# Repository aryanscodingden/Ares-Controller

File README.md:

## Ares - A game controller
A custom game controller built using a ESP32. 

This project was built because I always wanted to own a controller & decided to build one instead. 
It was indeed a very intersting journey to build one of my own, started to appricate the small QOL of other products.
<br>
(P.S. This is my first ever hardware project)

# Schematic

This schematic was made in KiCAD. It's a very simple controller.
<br>
It features a ESP32-NodeMCU for the main controller board & a TP4056 Module to charge the entire controller.

# PCB

# Case
This case was designed in Fusion 360. 

# Firmware

The firmware is written in C++ and will be edited/deployed from Arduino IDE.

# BOM
| SR NO | Item | Unit Price | URL |
|------:|------|-----------:|-----|
| 1 | ESP 32 NODE-MCU | ₹383 ($4.06) | https://robocraze.com/products/nodemcu-32-wifi-bluetooth-esp32-development-board30-pin |
| 2 | Joysticks | ₹269 ($2.85) | https://www.amazon.in/Robocraze-Joystick-Module-PS2-Set/dp/B086VZH739 |
| 3 | TP4056 | ₹14 ($0.15) | https://robocraze.com/products/tp4056-battery-charger-c-type-module-with-protection-1 |
| 4 | Tactile Push Button Switch Assorted Kit | ₹156 ($1.65) | https://robocraze.com/products/tactile-push-button-switch-assorted-kit-25-pieces-pack |
| 5 | Right Angle Tactile Triggers | ₹383 ($4.06) | https://www.amazon.in/Push-Button-Tactile-Switch-Height/dp/B08P5BN7JM |
| 6 | SPST Switches | ₹74 ($0.78) | https://www.amazon.in/Panel-Mount-Momentary-Button-Switch/dp/B0B54XV8D2 |
| 7 | 18650 Battery | ₹217 ($2.30) | https://robu.in/product/bak-nmc-18650-2600mah-3c-lithium-ion-3-6v-battery/ |
| 8 | 18650 Battery Holder | ₹16 ($0.17) | https://robocraze.com/products/18650-1-cell-holder |
| 9 | PCB | ₹2,138 ($22.61) | robu.in |
| 10 | 3D Print | ₹699 ($7.08) | https://www.amazon.in/PLA-3D-Flexibility-Eco-Friendly-Compatible/dp/B071D82LDV |
| **Total** |  | **₹4,349 ($45)** | |

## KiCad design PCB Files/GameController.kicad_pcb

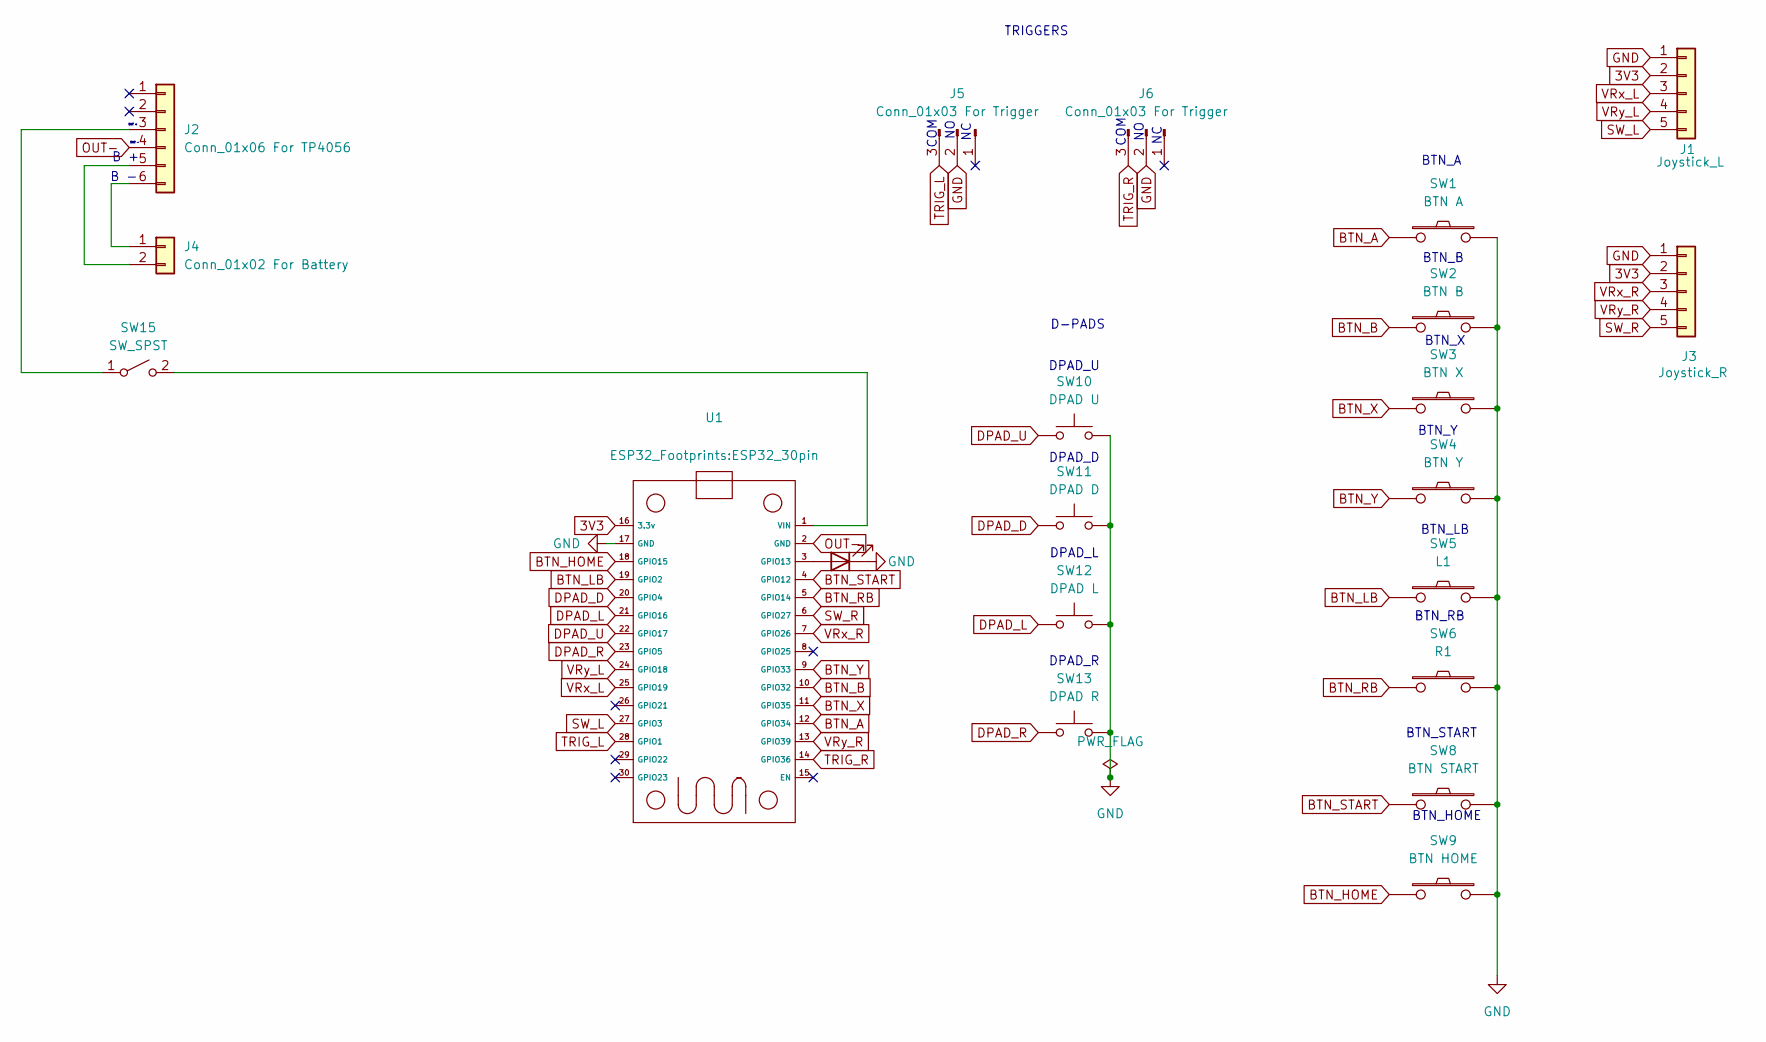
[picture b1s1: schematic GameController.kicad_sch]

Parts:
D1: LED; LED_D5.0mm_Horizontal_O6.35mm_Z3.0mm
J1: Joystick_L; PinHeader_1x05_P2.54mm_Horizontal
J2: Conn_01x06 For TP4056; TP4056-Module
J3: Joystick_R; PinHeader_1x05_P2.54mm_Horizontal
J4: Conn_01x02 For Battery; PinHeader_1x02_P2.54mm_Vertical
J5, J6: Conn_01x03 For Trigger
SW1: BTN A; SW_VS-1213-67-160GF
SW2: BTN B; SW_VS-1213-67-160GF
SW3: BTN X; SW_VS-1213-67-160GF
SW4: BTN Y; SW_VS-1213-67-160GF
SW5: L1; SW_Tactile_SKHH_Angled
SW6: R1; SW_Tactile_SKHH_Angled
SW8: BTN START; SW_VS-1213-67-160GF
SW9: BTN HOME; SW_VS-1213-67-160GF
SW10: DPAD U; SW_VS-1213-67-160GF
SW11: DPAD D; SW_VS-1213-67-160GF
SW12: DPAD L; SW_VS-1213-67-160GF
SW13: DPAD R; SW_VS-1213-67-160GF
SW15: SW_SPST; PinHeader_1x02_P2.54mm_Vertical
U1: ESP32_30pin

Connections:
3V3: J1.2, J3.2, U1.16 (3.3v)
BTN_A: SW1.1, U1.12 (GPIO34)
BTN_B: SW2.1, U1.10 (GPIO32)
BTN_HOME: SW9.1, U1.18 (GPIO15)
BTN_LB: SW5.1, U1.19 (GPIO2)
BTN_RB: SW6.1, U1.5 (GPIO14)
BTN_START: SW8.1, U1.4 (GPIO12)
BTN_X: SW3.1, U1.11 (GPIO35)
BTN_Y: SW4.1, U1.9 (GPIO33)
DPAD_D: SW11.1, U1.20 (GPIO4)
DPAD_L: SW12.1, U1.21 (GPIO16)
DPAD_R: SW13.1, U1.23 (GPIO5)
DPAD_U: SW10.1, U1.22 (GPIO17)
GND: D1.1 (K), J1.1, J3.1, J5.2, J6.2, SW1.2, SW2.2, SW3.2, SW4.2, SW5.2, SW6.2, SW8.2, SW9.2, SW10.2, SW11.2, SW12.2, SW13.2, U1.17 (GND)
unnamed: D1.2 (A), U1.3 (GPIO13)
unnamed: J2.3, SW15.1 (A)
unnamed: J2.5, J4.2
unnamed: J2.6, J4.1
unnamed: SW15.2 (B), U1.1 (VIN)
OUT-: J2.4, U1.2 (GND)
SW_L: J1.5, U1.27 (GPIO3)
SW_R: J3.5, U1.6 (GPIO27)
TRIG_L: J5.3, U1.28 (GPIO1)
TRIG_R: J6.3, U1.14 (GPIO36)
VRx_L: J1.3, U1.25 (GPIO19)
VRx_R: J3.3, U1.7 (GPIO26)
VRy_L: J1.4, U1.24 (GPIO18)
VRy_R: J3.4, U1.13 (GPIO39)

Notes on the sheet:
DPAD_L
DPAD_D
BTN_LB
BTN_A
B -
DPAD_R
BTN_Y
B +
BTN_START
DPAD_U
BTN_RB
COM
D-PADS
OUT +
OUT -
TRIGGERS
BTN_B
BTN_HOME
BTN_X

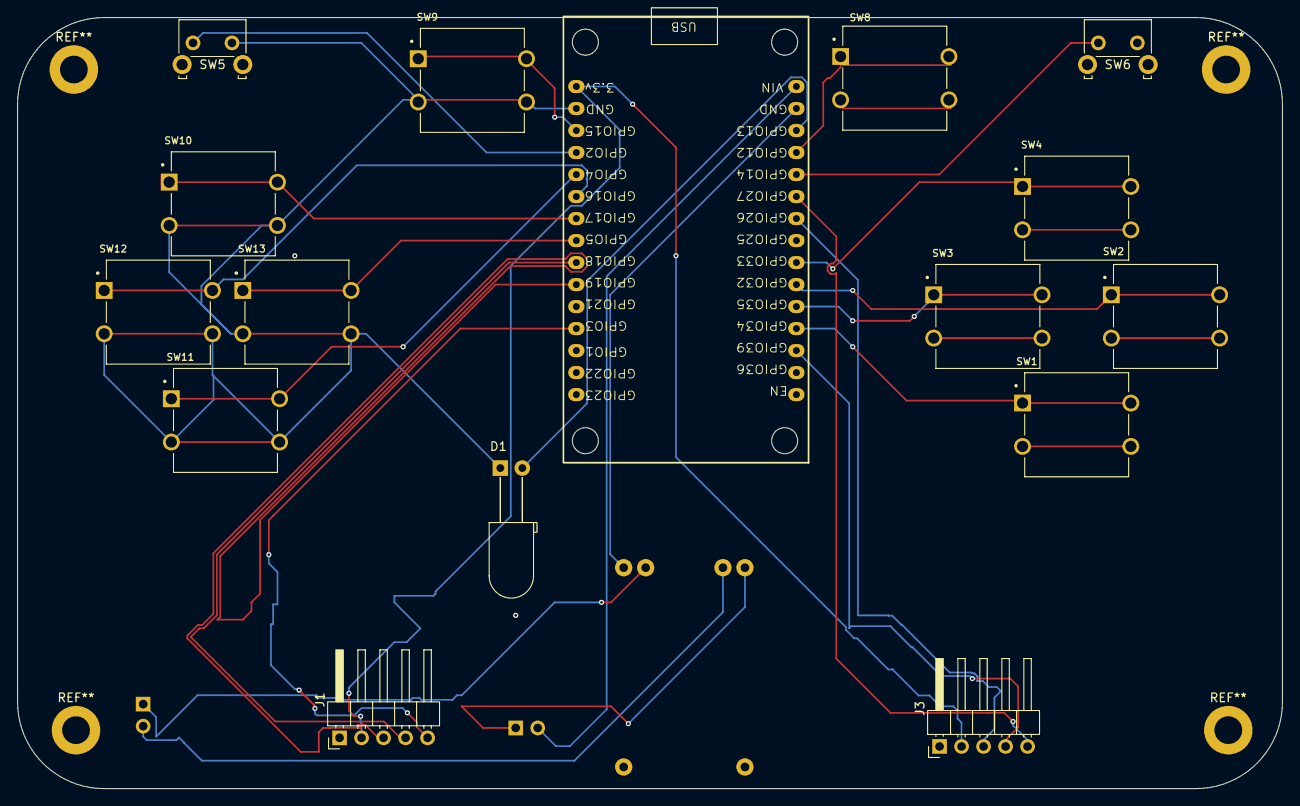
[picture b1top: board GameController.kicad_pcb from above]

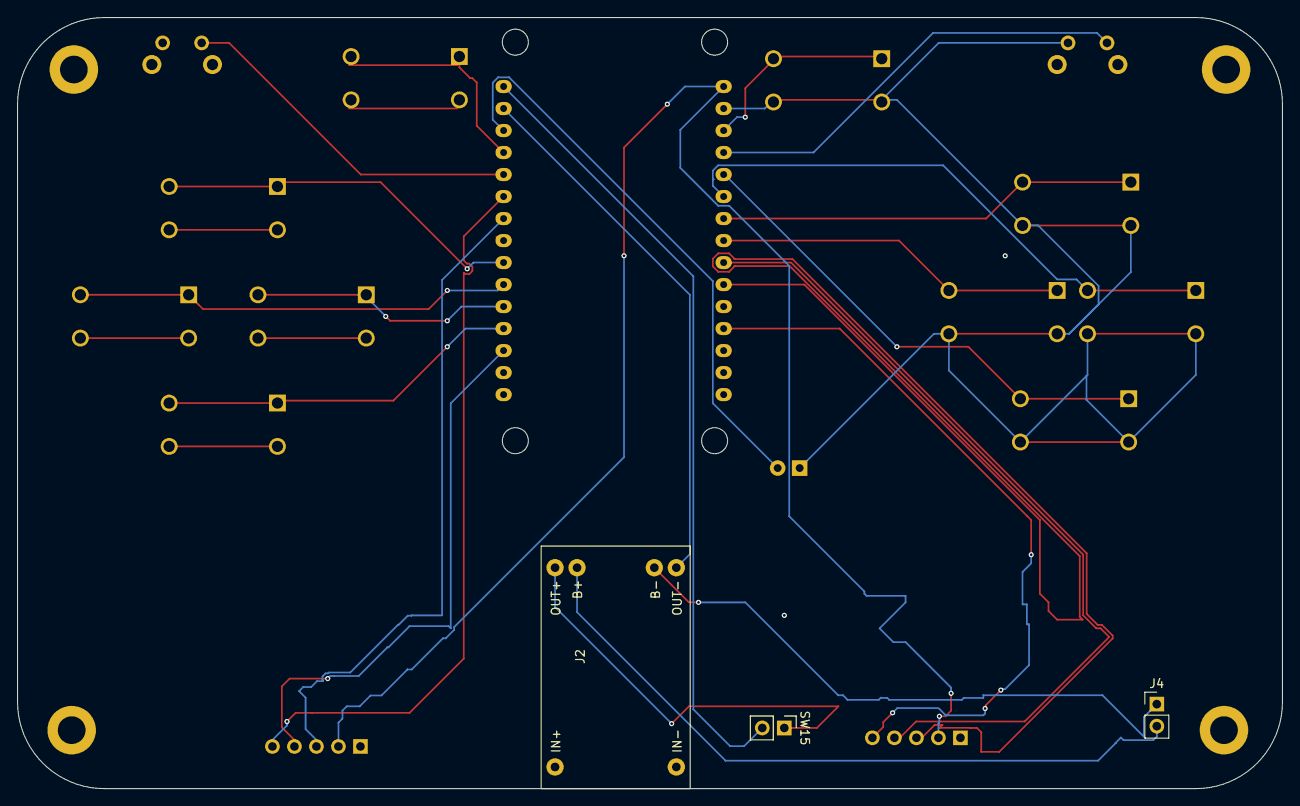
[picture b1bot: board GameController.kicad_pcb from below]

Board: 2 copper layers, 146.0 x 89.0 mm, 19 parts (3 on the bottom side), 26 nets.

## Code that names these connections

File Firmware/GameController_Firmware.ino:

#include <BleGamepad.h>
// Initialize BLE Gamepad as Xbox Controller
BleGamepad bleGamepad("Xbox Wireless Controller", "Microsoft", 100);
// ESP32-C6 Analog Pin Mapping (Joysticks Only)
#define LEFT_STICK_X 39
#define LEFT_STICK_Y 18
#define RIGHT_STICK_X 26
#define RIGHT_STICK_Y 25
// Digital Buttons Configuration (Pin, BLE ID)
struct ButtonMapping {
uint8_t pin;
uint16_t gamepadButton;
};
ButtonMapping actionButtons[] = {
{34, BUTTON_1},  // A
{32, BUTTON_2},  // B
{33, BUTTON_3},  // X
{1, BUTTON_4},  // Y
{21, BUTTON_5},  // LB
{27, BUTTON_6},  // RB
{15,  BUTTON_9},  // Home Button
{12,  BUTTON_10}, // Start Button
};
const int numButtons = sizeof(actionButtons) / sizeof(ButtonMapping);
// Trigger Buttons
#define LEFT_TRIGGER_BTN 2
#define RIGHT_TRIGGER_BTN 14
// D-Pad Pin Assignments
#define DPAD_U 17
#define DPAD_D 4
#define DPAD_L 5
#define DPAD_R 19
void setup() {
  Serial.begin(115200);

pinMode(LEFT_STICK_X, INPUT);
pinMode(LEFT_STICK_Y, INPUT);
pinMode(RIGHT_STICK_X, INPUT);
pinMode(RIGHT_STICK_Y, INPUT);

  for (int i = 0; i < numButtons; i++) {
    pinMode(actionButtons[i].pin, INPUT_PULLUP);
  }

pinMode(LEFT_TRIGGER_BTN, INPUT_PULLUP);
pinMode(RIGHT_TRIGGER_BTN, INPUT_PULLUP);

pinMode(DPAD_U, INPUT_PULLUP);
pinMode(DPAD_D, INPUT_PULLUP);
pinMode(DPAD_L, INPUT_PULLUP);
pinMode(DPAD_R, INPUT_PULLUP);

// Configure BLE Gamepad reports
BleGamepadConfiguration bleGamepadConfig;
bleGamepadConfig.setAutoReport(false);
bleGamepadConfig.setWhichAxes(true, true, true, true, true, true, false, false);
bleGamepad.begin(&bleGamepadConfig);
Serial.println("ESP32-C6 Joystick Precision Patch Loaded!");
}
void loop() {
if (bleGamepad.isConnected()) {
// 1. Process Action & Xbox Guide buttons
for (int i = 0; i < numButtons; i++) {
if (digitalRead(actionButtons[i].pin) == LOW) {
bleGamepad.press(actionButtons[i].gamepadButton);
} else {
bleGamepad.release(actionButtons[i].gamepadButton);
}
}

if (digitalRead(LEFT_TRIGGER_BTN) == LOW) {
bleGamepad.setLeftTrigger(65535);
} else {
bleGamepad.setLeftTrigger(0);
}
if (digitalRead(RIGHT_TRIGGER_BTN) == LOW) {
bleGamepad.setRightTrigger(65535);
} else {
bleGamepad.setRightTrigger(0);
}
bool up = (digitalRead(DPAD_U) == LOW);
bool down = (digitalRead(DPAD_D) == LOW);
bool left = (digitalRead(DPAD_L) == LOW);
bool right = (digitalRead(DPAD_R) == LOW);
if (up && right) bleGamepad.setHat1(DPAD_UP_RIGHT);
else if (down && right) bleGamepad.setHat1(DPAD_DOWN_RIGHT);
else if (down && left) bleGamepad.setHat1(DPAD_DOWN_LEFT);
else if (up && left) bleGamepad.setHat1(DPAD_UP_LEFT);
else if (up) bleGamepad.setHat1(DPAD_UP);
else if (down) bleGamepad.setHat1(DPAD_DOWN);
else if (left) bleGamepad.setHat1(DPAD_LEFT);
else if (right) bleGamepad.setHat1(DPAD_RIGHT);
else bleGamepad.setHat1(HAT_CENTERED);
// Joysticks
int lsX = map(analogRead(LEFT_STICK_Y), 0, 4095, -32767, 32767);
int lsY = map(analogRead(LEFT_STICK_X), 0, 4095, -32767, 32767);
int rsX = map(analogRead(RIGHT_STICK_X), 0, 4095, -32767, 32767);
int rsY = map(analogRead(RIGHT_STICK_Y), 0, 4095, -32767, 32767);
bleGamepad.setLeftThumb(lsX, lsY);
bleGamepad.setRightThumb(rsX, rsY);
bleGamepad.sendReport();
delay(8);
}
}

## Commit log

2026-06-26 uploading files
2026-06-26 Add README for Ares game controller project
2026-06-26 add BOM.csv
2026-06-26 firmware update
2026-06-27 add f3z file
